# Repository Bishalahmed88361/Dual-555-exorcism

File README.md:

# dual-555
LED flashing with increased OFF intervals using dual NE555D. Flash is brief and OFF state is increased.

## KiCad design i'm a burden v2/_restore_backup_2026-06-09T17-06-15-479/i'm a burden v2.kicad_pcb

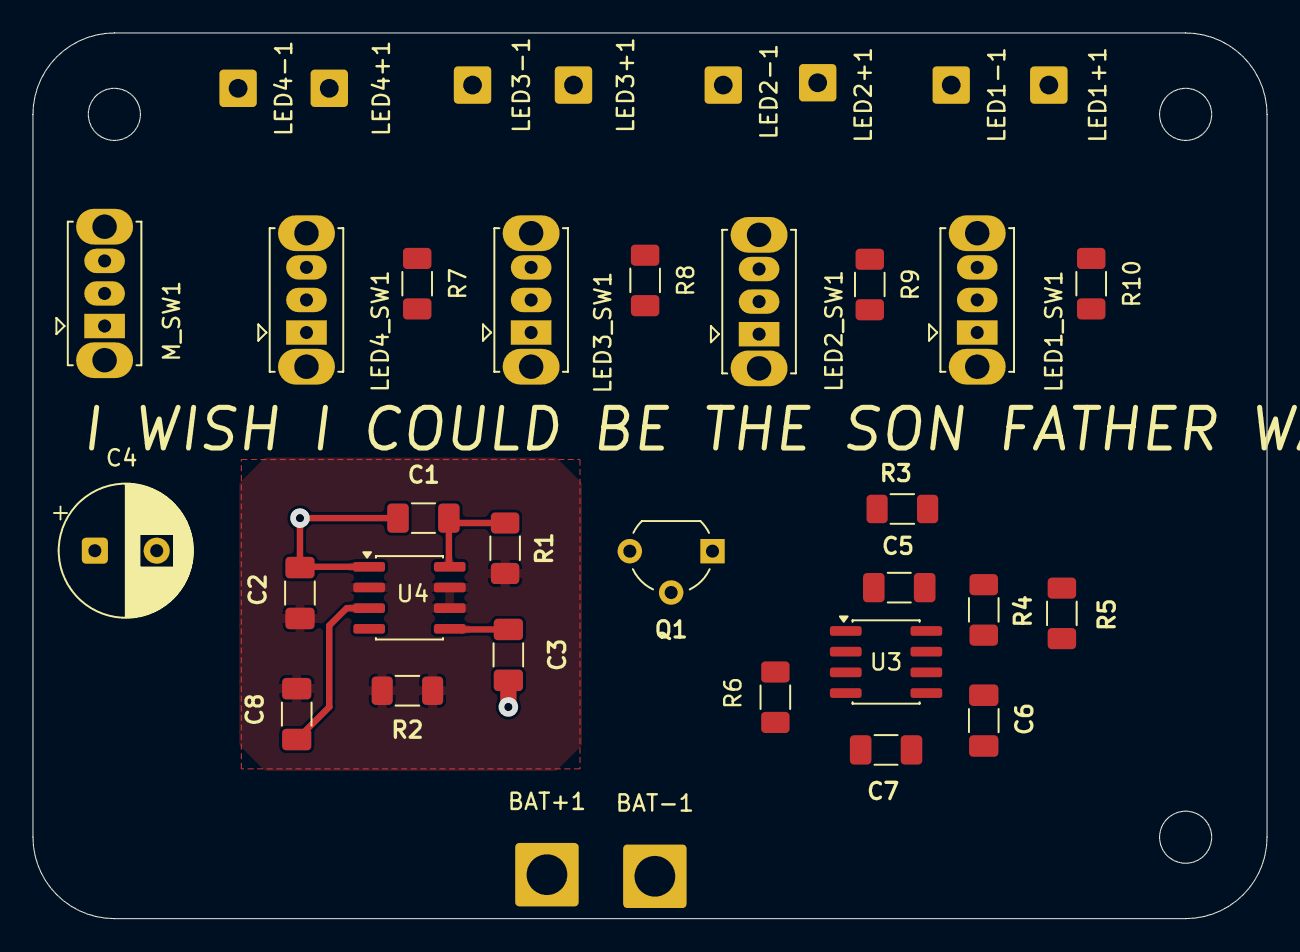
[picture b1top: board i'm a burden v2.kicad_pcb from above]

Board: 2 copper layers, 75.8 x 54.4 mm, 40 parts (0 on the bottom side), 12 nets.

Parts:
BAT+1: Conn_01x01; SolderWire-2sqmm_1x01_D2mm_OD3.9mm
BAT-1: Conn_01x01; SolderWire-2sqmm_1x01_D2mm_OD3.9mm
C1, C5, C8: 100nf; C_1206_3216Metric_Pad1.33x1.80mm_HandSolder
C2, C7: 10uf; C_1206_3216Metric_Pad1.33x1.80mm_HandSolder
C3, C6: 10nf; C_1206_3216Metric_Pad1.33x1.80mm_HandSolder
C4: 47uf; CP_Radial_D8.0mm_P3.80mm
H1, H2, H3, H4: MountingHole; MountingHole_3.2mm_M3
LED1+1, LED1-1, LED2+1, LED2-1, LED3+1, LED3-1, LED4+1, LED4-1: Conn_01x01; SolderWire-0.5sqmm_1x01_D0.9mm_OD2.3mm
LED1_SW1, LED2_SW1, LED3_SW1, LED4_SW1: SW_SPDT; SW_Slide_SPDT_Straight_CK_OS102011MS2Q
M_SW1: SW_SPDT; SW_Slide_SPDT_Straight_CK_OS102011MS2Q
Q1: BC547; TO-92_Wide
R1, R3, R5: 10k; R_1206_3216Metric_Pad1.30x1.75mm_HandSolder
R2: 220ohm; R_1206_3216Metric_Pad1.30x1.75mm_HandSolder
R4: 68k; R_1206_3216Metric_Pad1.30x1.75mm_HandSolder
R6: 4.7k; R_1206_3216Metric_Pad1.30x1.75mm_HandSolder
R7, R8, R9, R10: 330ohm; R_1206_3216Metric_Pad1.30x1.75mm_HandSolder
U3, U4: NE555D; SOIC-8_3.9x4.9mm_P1.27mm

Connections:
/+: BAT+1.1 (Pin_1_1), C1.1, C4.1, LED1+1.1 (Pin_1_1), LED1_SW1.2 (B), LED1_SW1.3 (C), LED2+1.1 (Pin_1_1), LED2_SW1.2 (B), LED2_SW1.3 (C), LED3+1.1 (Pin_1_1), LED3_SW1.2 (B), LED3_SW1.3 (C), LED4+1.1 (Pin_1_1), LED4_SW1.2 (B), LED4_SW1.3 (C), M_SW1.2 (B), M_SW1.3 (C), R1.1, R7.1, R7.2, R8.1, R8.2, R9.1, R9.2, R10.1, R10.2, U3.4 (~RST), U4.4 (~RST), U4.8 (VCC)
/-: BAT-1.1 (Pin_1_1), C1.2, C2.1, C3.2, C4.2, C5.2, C6.2, C7.2, Q1.3 (E), U3.1 (GND), U4.1 (GND)
/Bridged: C2.2, C8.2, R1.2, R2.1, R2.2, U4.2 (TRIG), U4.6 (THRES), U4.7 (DISCH)
/T_B: Q1.2 (B), R6.2
/T_C: LED1-1.1 (Pin_1_1), LED2-1.1 (Pin_1_1), LED3-1.1 (Pin_1_1), LED4-1.1 (Pin_1_1), Q1.1 (C)
/U1_OUT: C8.1, U4.3 (OUT)
/U2_TRIG: R3.2, U3.2 (TRIG)
unnamed: C6.1, U3.5 (CONT)
unnamed: C7.1, R4.2, R5.2, U3.6 (THRES), U3.7 (DISCH)
unnamed: R6.1, U3.3 (OUT)
unnamed: C5.1, R3.1, R4.1, R5.1, U3.8 (VCC)
unnamed: C3.1, U4.5 (CONT)

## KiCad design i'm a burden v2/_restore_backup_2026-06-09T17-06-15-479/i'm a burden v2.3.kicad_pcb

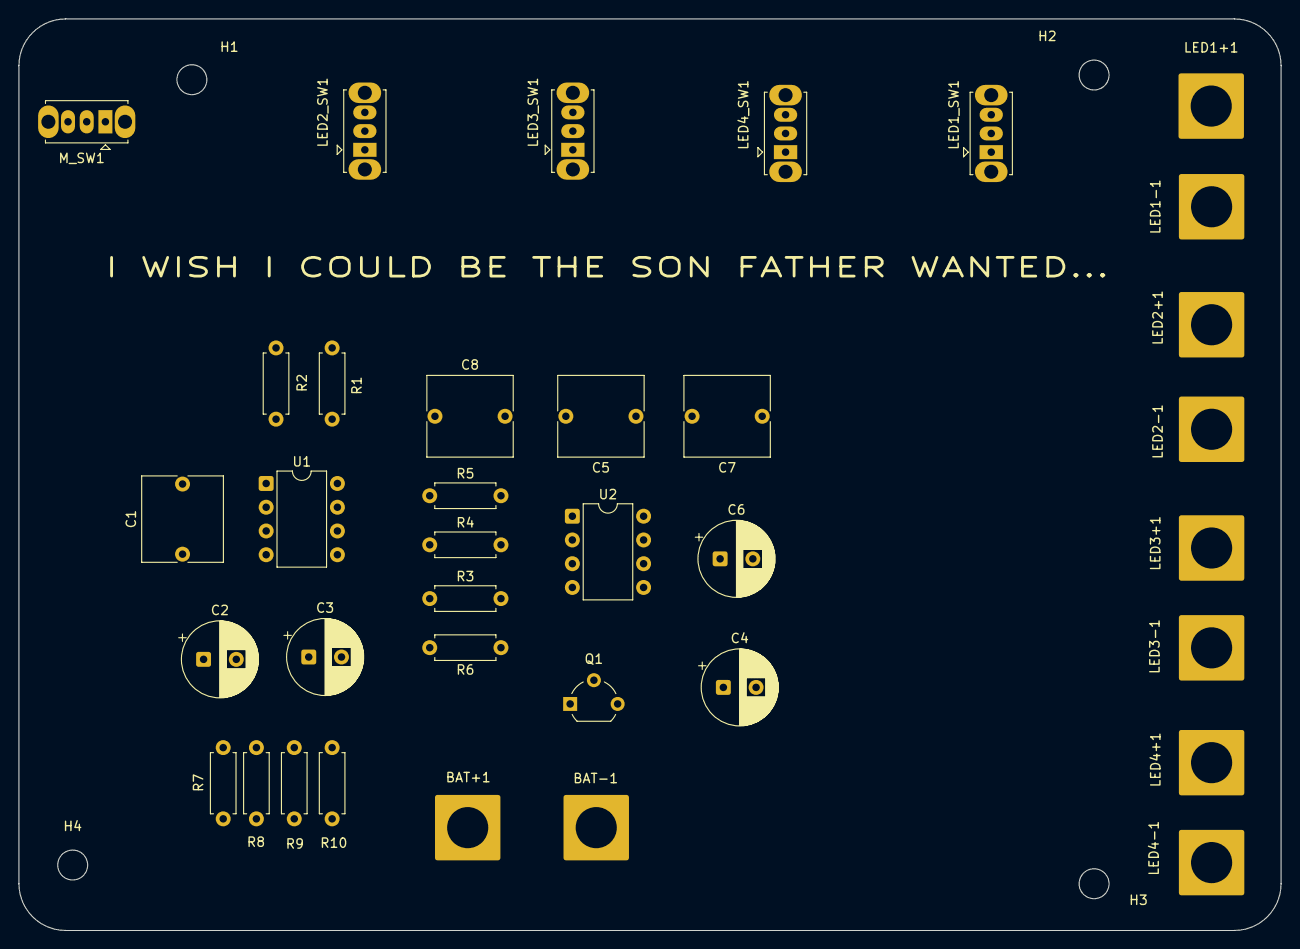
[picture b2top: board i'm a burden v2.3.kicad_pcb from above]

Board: 2 copper layers, 135.0 x 97.5 mm, 40 parts (0 on the bottom side), 22 nets, no tracks yet.

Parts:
BAT+1: Conn_01x01; SolderWire-6sqmm_1x01_D3.5mm_OD7mm
BAT-1: Conn_01x01; SolderWire-6sqmm_1x01_D3.5mm_OD7mm
C1, C5, C8: 100nf; C_Rect_L9.0mm_W8.5mm_P7.50mm_MKT
C2: 10uf; CP_Radial_D8.0mm_P3.50mm
C3, C6: 10nf; CP_Radial_D8.0mm_P3.50mm
C4: 47uf; CP_Radial_D8.0mm_P3.50mm
C7: 10uf; C_Rect_L9.0mm_W8.5mm_P7.50mm_MKT
H1, H2, H3, H4: MountingHole; MountingHole_3.2mm_M3
LED1+1, LED1-1, LED2+1, LED2-1, LED3+1, LED3-1, LED4+1, LED4-1: Conn_01x01; SolderWire-6sqmm_1x01_D3.5mm_OD7mm
LED1_SW1, LED2_SW1, LED3_SW1, LED4_SW1: SW_SPDT; SW_Slide_SPDT_Straight_CK_OS102011MS2Q
M_SW1: SW_SPDT; SW_Slide_SPDT_Straight_CK_OS102011MS2Q
Q1: BC547; TO-92_Wide
R1, R3, R5: 10k; R_Axial_DIN0207_L6.3mm_D2.5mm_P7.62mm_Horizontal
R2: 220ohm; R_Axial_DIN0207_L6.3mm_D2.5mm_P7.62mm_Horizontal
R4: 68k; R_Axial_DIN0207_L6.3mm_D2.5mm_P7.62mm_Horizontal
R6: 4.7k; R_Axial_DIN0207_L6.3mm_D2.5mm_P7.62mm_Horizontal
R7, R8, R9, R10: 330ohm; R_Axial_DIN0207_L6.3mm_D2.5mm_P7.62mm_Horizontal
U1, U2: NE555P; DIP-8_W7.62mm

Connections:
/+: C1.1, C4.1, LED1_SW1.2 (B), LED2_SW1.2 (B), LED3_SW1.2 (B), LED4_SW1.2 (B), M_SW1.3 (C), R1.1, U1.4 (~RST), U1.8 (VCC), U2.4 (~RST)
/-: BAT-1.1 (Pin_1_1), C1.2, C2.1, C3.2, C4.2, C5.2, C6.2, C7.2, Q1.3 (E), U1.1 (GND), U2.1 (GND)
/LED-: LED1-1.1 (Pin_1_1), LED2-1.1 (Pin_1_1), LED3-1.1 (Pin_1_1), LED4-1.1 (Pin_1_1), Q1.1 (C)
/T_B: Q1.2 (B), R6.2
/U1_OUT: C8.1, U1.3 (OUT)
/U2_TRIG: C8.2, R3.2, U2.2 (TRIG)
unnamed: BAT+1.1 (Pin_1_1), M_SW1.2 (B)
unnamed: LED1+1.1 (Pin_1_1), R10.2
unnamed: LED1_SW1.3 (C), R10.1
unnamed: LED2+1.1 (Pin_1_1), R9.2
unnamed: LED2_SW1.3 (C), R9.1
unnamed: LED3+1.1 (Pin_1_1), R7.1
unnamed: LED3_SW1.3 (C), R7.2
unnamed: LED4+1.1 (Pin_1_1), R8.2
unnamed: LED4_SW1.3 (C), R8.1
unnamed: C3.1, U1.5 (CONT)
unnamed: R1.2, R2.1, U1.7 (DISCH)
unnamed: C2.2, R2.2, U1.2 (TRIG), U1.6 (THRES)
unnamed: C6.1, U2.5 (CONT)
unnamed: C7.1, R4.2, R5.2, U2.6 (THRES), U2.7 (DISCH)
unnamed: R6.1, U2.3 (OUT)
unnamed: C5.1, R3.1, R4.1, R5.1, U2.8 (VCC)

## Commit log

2026-06-11 my first PCB project with dual 555 IC
2026-06-11 Ignore editor history folders
2026-06-14 Add brief description of LED flashing project
